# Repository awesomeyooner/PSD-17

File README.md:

# PSD-17

The PSD-21 is an FOC controller designed for stepper motors, specifically for NEMA 17 stepper motors.

Click here for the [manual](./docs/Manual.md)
## Folder Tree

```bash
.
├── esp_test_firmware # Test firmware on ESP32
│   └── firmware # PlatformIO Project
├── firmware # Main firmware (SAMD21)
├── i2c_test # I2C Master Communication Test
│   └── project  # CMake Project
├── pcb # KiCad Project
├── samd21_test_firmware # Test firmware on SAMD21
│   └── firmware # PlatformIO Project
└── README.md
```

## Hardware Details

- [NEMA 17 Motor](https://www.omc-stepperonline.com/nema-17-stepper-motor)
    - [STEPPERONLINE 23mm](https://www.amazon.com/dp/B0B93PNYCP?ref=ppx_yo2ov_dt_b_fed_asin_title&th=1)
    - [STEPPERONLINE 38mm](https://www.amazon.com/dp/B0B38GX54H?ref=ppx_yo2ov_dt_b_fed_asin_title&th=1)
- [AS5047P Magnetic Encoder](https://www.digikey.com/en/products/detail/ams-osram-usa-inc/AS5047P-ADAPTERBOARD/5452344?s=N4IgTCBcDaIIYGcCsAGALAdgA4gLoF8g)
    - [Diametric Magnet](https://www.digikey.com/en/products/detail/radial-magnets-inc/9049/6030786) (6mm x 2.5mm )
- [DRV8874 DC Motor Driver](https://www.pololu.com/product/4035) (2x)
- [SAMD21 Seeed Studio Xiao](https://www.amazon.com/Seeeduino-Smallest-Microcontroller-Interfaces-Compatible/dp/B08745JBRP?th=1)

### Passive Components 

- [5V Voltage Regulator](https://www.pololu.com/product/5433?gQT=1)

## Datasheets

### AS5047P
- [Board](https://www.mouser.com/datasheet/2/588/AS5047P-TS_EK_AB_Operation-Manual_Rev.1.0-775823.pdf)
- [Chip](https://look.ams-osram.com/m/d05ee39221f9857/original/AS5047P-DS000324.pdf)

### DRV8874
- [Board](https://www.pololu.com/product/4035)
- [Chip](https://www.ti.com/lit/ds/symlink/drv8874.pdf)

### SAMD21
- [Seeed Studio Xiao](https://wiki.seeedstudio.com/Seeeduino-XIAO/)
- [SAMD21 Chip](https://ww1.microchip.com/downloads/en/DeviceDoc/SAM_D21_DA1_Family_DataSheet_DS40001882F.pdf)

### NEMA 17
- [23mm](https://www.omc-stepperonline.com/e-series-nema-17-bipolar-1-8deg-17ncm-24-07oz-in-1a-42x42x23mm-4-wires-17he08-1004s)
- [38mm](https://www.omc-stepperonline.com/e-series-nema-17-bipolar-42ncm-59-49oz-in-1-5a-42x42x38mm-4-wires-w-1m-cable-connector-17he15-1504s)

## Contact
Feel free to reach out!
- awesomeyooner@gmail.com

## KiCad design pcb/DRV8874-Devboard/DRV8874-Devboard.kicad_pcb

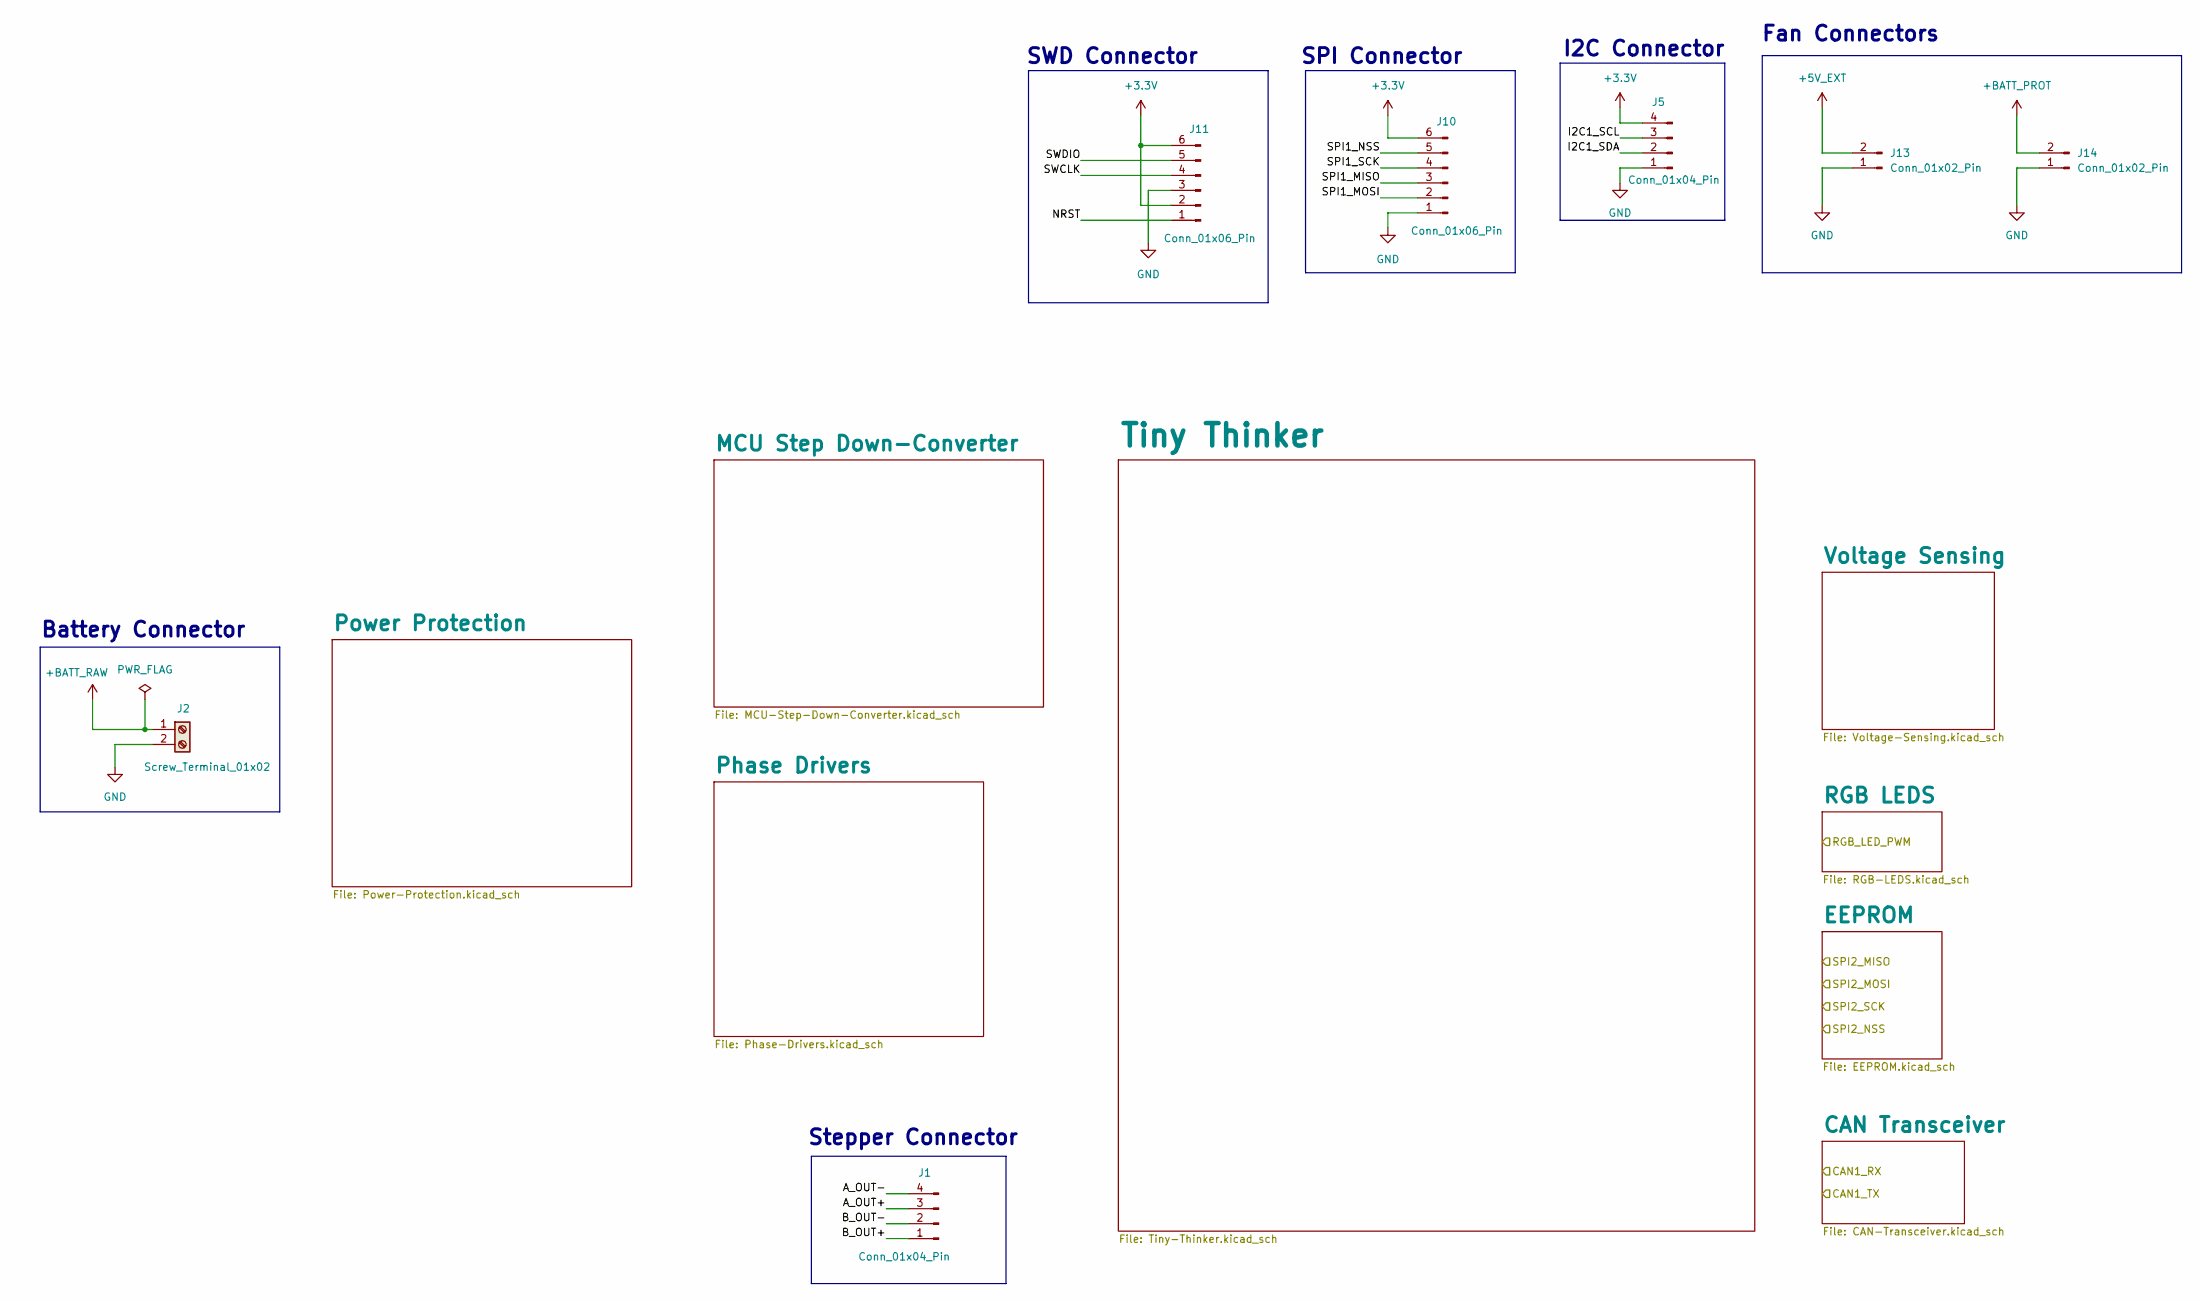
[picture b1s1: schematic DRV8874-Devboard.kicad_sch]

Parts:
J1, J5: Conn_01x04_Pin; PinHeader_1x04_P2.54mm_Vertical
J2: Screw_Terminal_01x02; CONN-TH_2P-P5.08_DB128L-5.08-2P-BK-S; JLCPCB Part # C430601
J10, J11: Conn_01x06_Pin; PinHeader_1x06_P2.54mm_Vertical
J13, J14: Conn_01x02_Pin; PinHeader_1x02_P2.54mm_Vertical

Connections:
+3.3V: J5.4, J10.6, J11.2, J11.6; also elsewhere on the board
+5V_EXT: J13.2; also elsewhere on the board
+BATT_PROT: J14.2; also elsewhere on the board
+BATT_RAW: J2.1; also elsewhere on the board
/A_OUT+: J1.3
/A_OUT-: J1.4
/B_OUT+: J1.1
/B_OUT-: J1.2
/I2C1_SCL: J5.3
/I2C1_SDA: J5.2
/NRST: J11.1
/SPI1_MISO: J10.3
/SPI1_MOSI: J10.2
/SPI1_NSS: J10.5
/SPI1_SCK: J10.4
/SWCLK: J11.4
/SWDIO: J11.5
GND: J2.2, J5.1, J10.1, J11.3, J13.1, J14.1; also elsewhere on the board

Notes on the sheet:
SWD Connector
Fan Connectors
Battery Connector
SPI Connector
Stepper Connector
I2C Connector

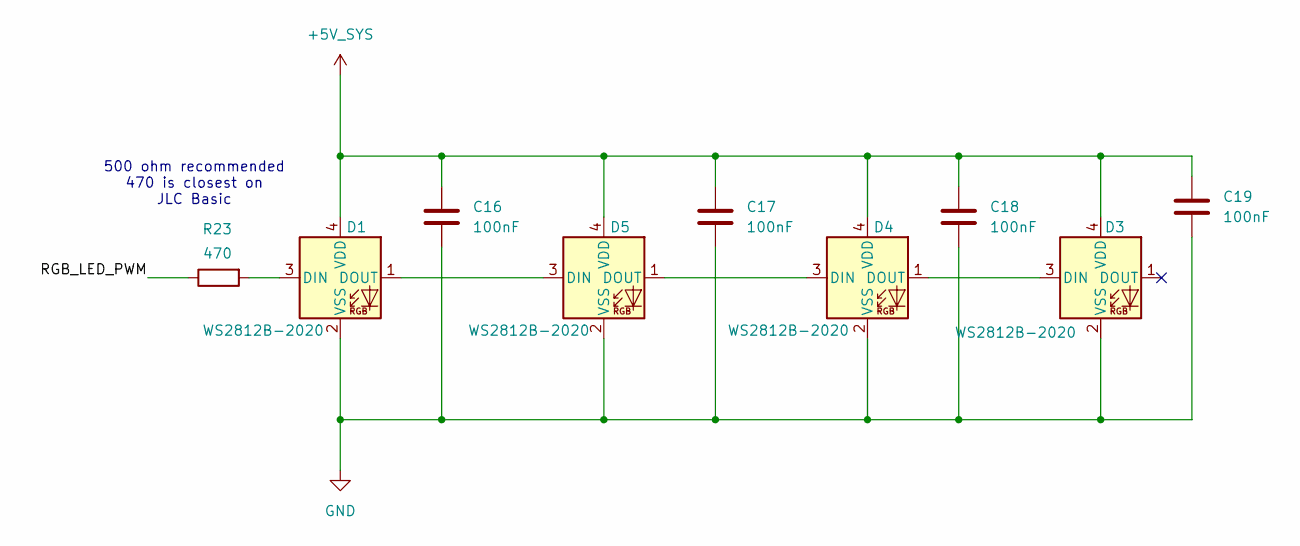
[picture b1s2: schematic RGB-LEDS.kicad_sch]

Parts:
C16, C17, C18, C19: 100nF; C_0402_1005Metric; JLCPCB Part # C307331
D1, D3, D4, D5: WS2812B-2020; LED_WS2812B-2020_PLCC4_2.0x2.0mm; JLCPCB Part # C3646929
R23: 470; R_0402_1005Metric; JLCPCB Part # C25117

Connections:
+5V_SYS: C16.1, C17.1, C18.1, C19.1, D1.4 (VDD), D3.4 (VDD), D4.4 (VDD), D5.4 (VDD); also elsewhere on the board
/RGB LEDS/RGB_LED_PWM: R23.1
GND: C16.2, C17.2, C18.2, C19.2, D1.2 (VSS), D3.2 (VSS), D4.2 (VSS), D5.2 (VSS); also elsewhere on the board
unnamed: D1.3 (DIN), R23.2
unnamed: D1.1 (DOUT), D5.3 (DIN)
unnamed: D3.3 (DIN), D4.1 (DOUT)
unnamed: D4.3 (DIN), D5.1 (DOUT)

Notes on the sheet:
500 ohm recommended 470 is closest on JLC Basic

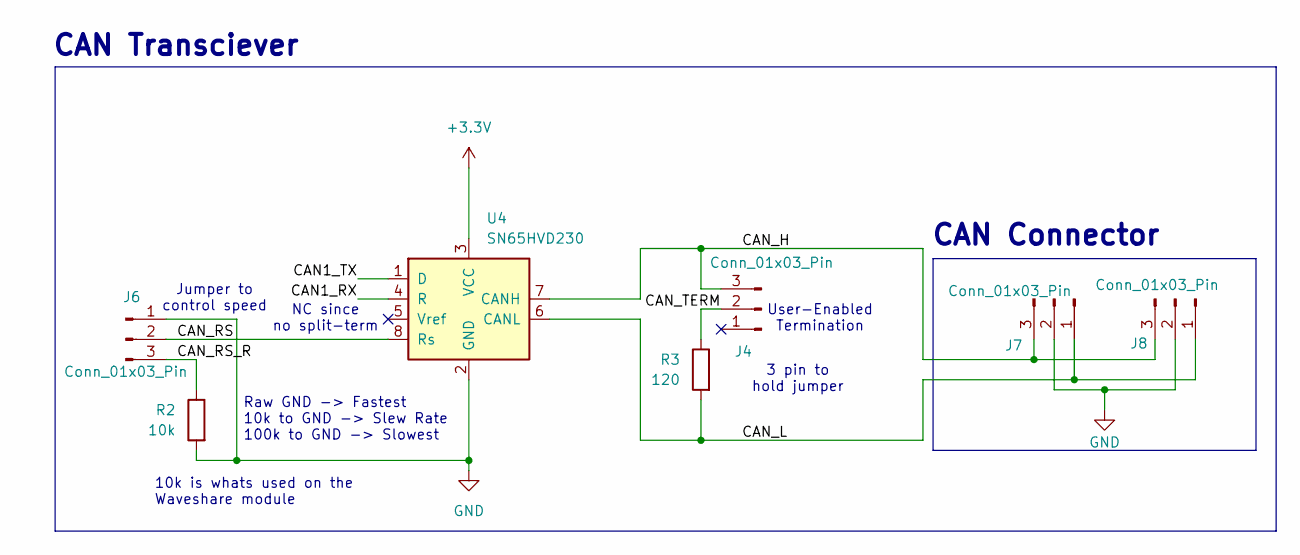
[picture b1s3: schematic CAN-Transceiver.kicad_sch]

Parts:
J4, J6, J7, J8: Conn_01x03_Pin; PinHeader_1x03_P2.54mm_Vertical
R2: 10k; R_0402_1005Metric; JLCPCB Part # C25744
R3: 120; R_0402_1005Metric; JLCPCB Part # C25079
U4: SN65HVD230; SOIC-8_3.9x4.9mm_P1.27mm; JLCPCB Part # C12084

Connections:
+3.3V: U4.3 (VCC); also elsewhere on the board
/CAN Transceiver/CAN1_RX: U4.4 (R)
/CAN Transceiver/CAN1_TX: U4.1 (D)
/CAN Transceiver/CAN_H: J4.3, J7.3, J8.3, U4.7 (CANH)
/CAN Transceiver/CAN_L: J7.1, J8.1, R3.2, U4.6 (CANL)
/CAN Transceiver/CAN_RS: J6.2, U4.8 (Rs)
/CAN Transceiver/CAN_RS_R: J6.3, R2.1
/CAN Transceiver/CAN_TERM: J4.2, R3.1
GND: J6.1, J7.2, J8.2, R2.2, U4.2 (GND); also elsewhere on the board

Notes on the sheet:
Jumper to control speed
10k is whats used on the Waveshare module
CAN Connector
CAN Transciever
Raw GND -> Fastest 10k to GND -> Slew Rate 100k to GND -> Slowest
3 pin to hold jumper
User-Enabled Termination
NC since no split-term

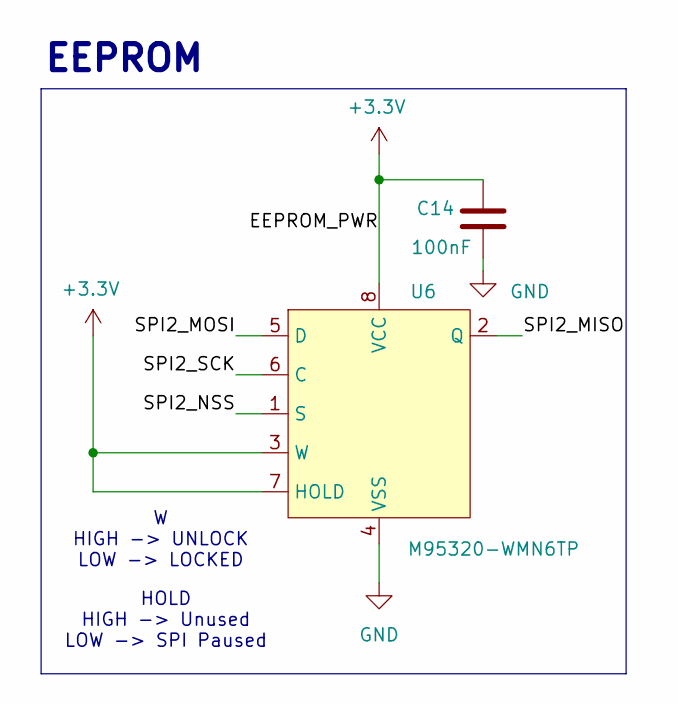
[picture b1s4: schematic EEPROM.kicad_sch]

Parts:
C14: 100nF; C_0402_1005Metric; JLCPCB Part # C307331
U6: M95320-WMN6TP; SO-8_3.9x4.9mm_P1.27mm; JLCPCB Part # C283459

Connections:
+3.3V: C14.1, U6.3 (W), U6.7 (HOLD), U6.8 (VCC); also elsewhere on the board
/EEPROM/SPI2_MISO: U6.2 (Q)
/EEPROM/SPI2_MOSI: U6.5 (D)
/EEPROM/SPI2_NSS: U6.1 (S)
/EEPROM/SPI2_SCK: U6.6 (C)
GND: C14.2, U6.4 (VSS); also elsewhere on the board

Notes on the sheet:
HOLD HIGH -> Unused LOW -> SPI Paused
EEPROM
W HIGH -> UNLOCK LOW -> LOCKED

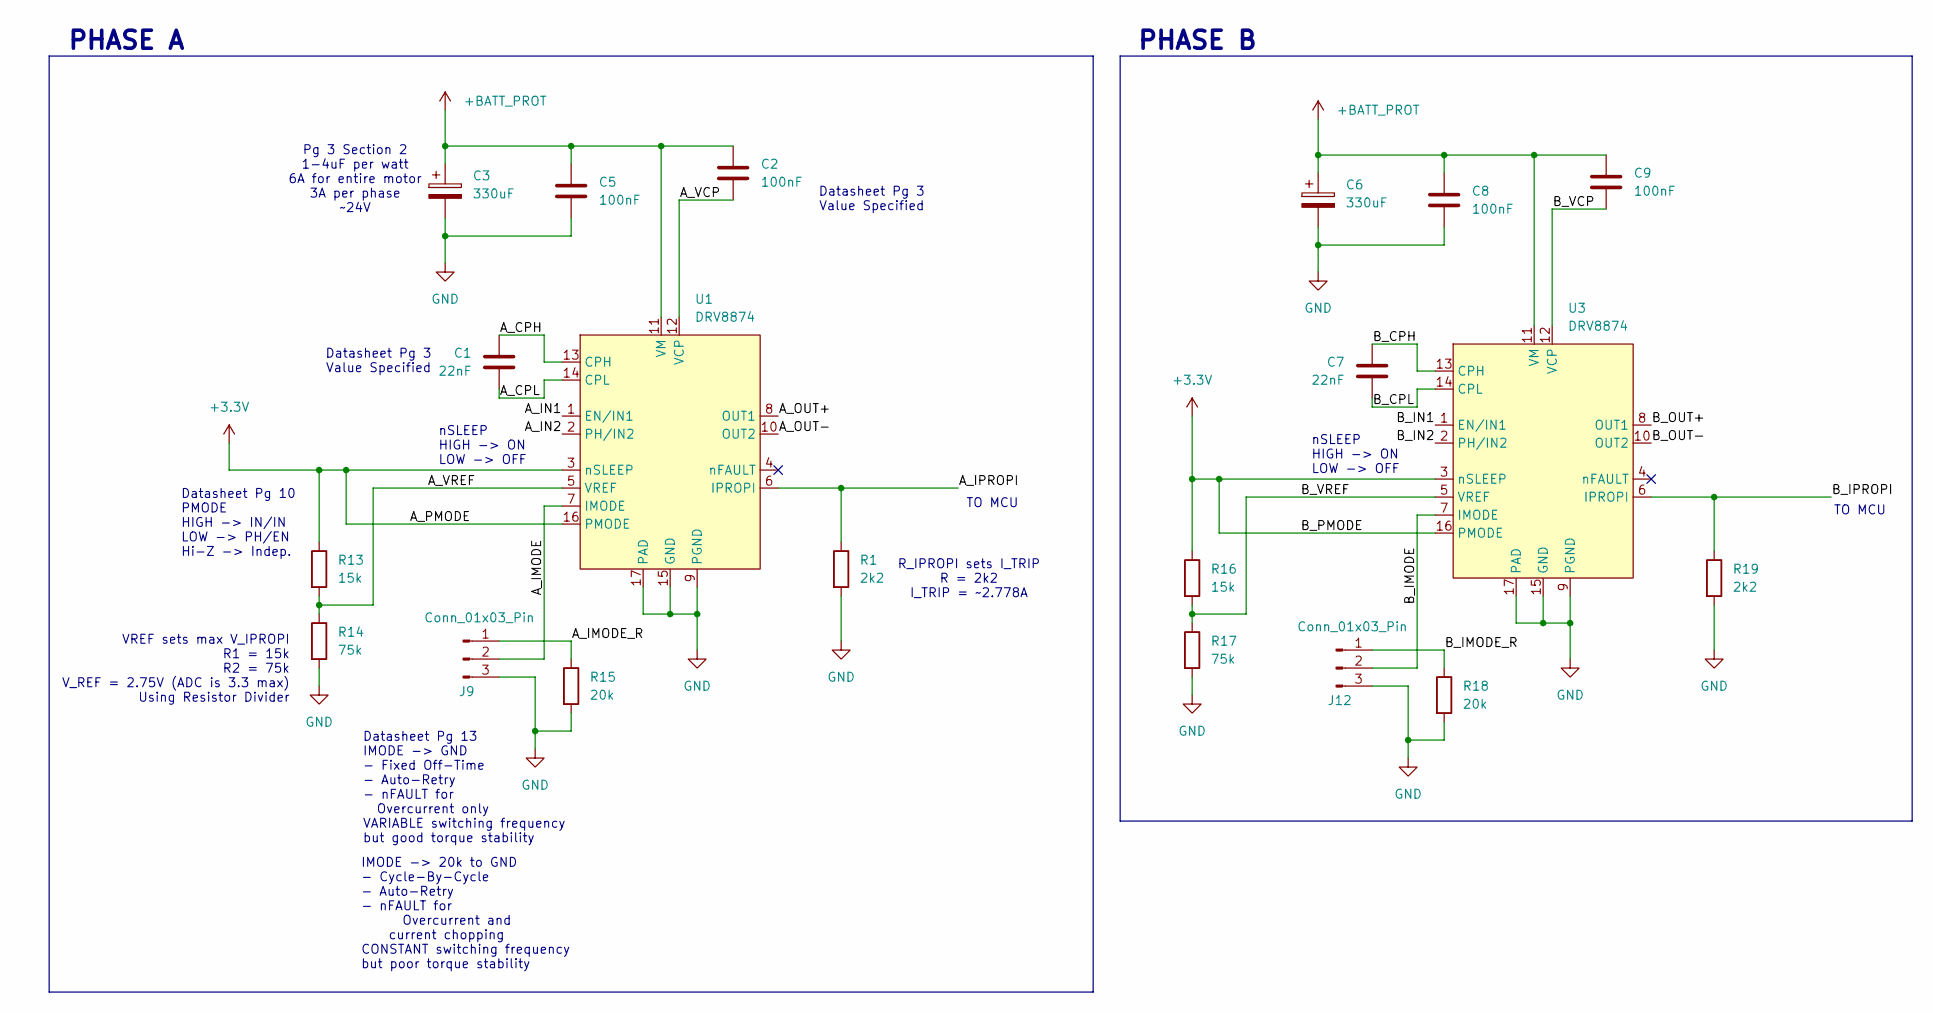
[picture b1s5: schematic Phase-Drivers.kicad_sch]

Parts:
C1, C7: 22nF; C_0402_1005Metric; JLCPCB Part # C1532
C2, C5, C8, C9: 100nF; C_0402_1005Metric; JLCPCB Part # C307331
C3, C6: 330uF; CP_Elec_10x10.5; JLCPCB Part # C46550419
J9, J12: Conn_01x03_Pin; PinHeader_1x03_P2.54mm_Vertical
R1, R19: 2k2; R_0402_1005Metric; JLCPCB Part # C25879
R13, R16: 15k; R_0603_1608Metric; JLCPCB Part # C22809
R14, R17: 75k; R_0603_1608Metric; JLCPCB Part # C23242
R15, R18: 20k; R_0603_1608Metric; JLCPCB Part # C4184
U1, U3: DRV8874; HTSSOP-16-1EP_4.4x5mm_P0.65mm_EP3.4x5mm_Mask2.46x2.31mm; JLCPCB Part # C1855818

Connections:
+3.3V: R13.1, R16.1, U1.3 (nSLEEP), U1.16 (PMODE), U3.3 (nSLEEP), U3.16 (PMODE); also elsewhere on the board
+BATT_PROT: C2.1, C3.1, C5.1, C6.1, C8.1, C9.1, U1.11 (VM), U3.11 (VM); also elsewhere on the board
/Phase Drivers/A_CPH: C1.1, U1.13 (CPH)
/Phase Drivers/A_CPL: C1.2, U1.14 (CPL)
/Phase Drivers/A_IMODE: J9.2, U1.7 (IMODE)
/Phase Drivers/A_IMODE_R: J9.1, R15.1
/Phase Drivers/A_IN1: U1.1 (EN/IN1)
/Phase Drivers/A_IN2: U1.2 (PH/IN2)
/Phase Drivers/A_IPROPI: R1.1, U1.6 (IPROPI)
/Phase Drivers/A_OUT+: U1.8 (OUT1)
/Phase Drivers/A_OUT-: U1.10 (OUT2)
/Phase Drivers/A_VCP: C2.2, U1.12 (VCP)
/Phase Drivers/A_VREF: R13.2, R14.1, U1.5 (VREF)
/Phase Drivers/B_CPH: C7.1, U3.13 (CPH)
/Phase Drivers/B_CPL: C7.2, U3.14 (CPL)
/Phase Drivers/B_IMODE: J12.2, U3.7 (IMODE)
/Phase Drivers/B_IMODE_R: J12.1, R18.1
/Phase Drivers/B_IN1: U3.1 (EN/IN1)
/Phase Drivers/B_IN2: U3.2 (PH/IN2)
/Phase Drivers/B_IPROPI: R19.1, U3.6 (IPROPI)
/Phase Drivers/B_OUT+: U3.8 (OUT1)
/Phase Drivers/B_OUT-: U3.10 (OUT2)
/Phase Drivers/B_VCP: C9.2, U3.12 (VCP)
/Phase Drivers/B_VREF: R16.2, R17.1, U3.5 (VREF)
GND: C3.2, C5.2, C6.2, C8.2, J9.3, J12.3, R1.2, R14.2, R15.2, R17.2, R18.2, R19.2, U1.9 (PGND), U1.15 (GND), U1.17 (PAD), U3.9 (PGND), U3.15 (GND), U3.17 (PAD); also elsewhere on the board

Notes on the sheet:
Datasheet Pg 3 Value Specified
PHASE B
Datasheet Pg 13 IMODE -> GND - Fixed Off-Time - Auto-Retry - nFAULT for Overcurrent only VARIABLE switching frequency but good torque stability
PHASE A
nSLEEP HIGH -> ON LOW -> OFF
VREF sets max V_IPROPI R1 = 15k R2 = 75k V_REF = 2.75V (ADC is 3.3 max) Using Resistor Divider
TO MCU
IMODE -> 20k to GND - Cycle-By-Cycle - Auto-Retry - nFAULT for Overcurrent and current chopping CONSTANT switching frequency but poor torque stability
Pg 3 Section 2 1-4uF per watt 6A for entire motor 3A per phase ~24V
R_IPROPI sets I_TRIP R = 2k2 I_TRIP = ~2.778A
Datasheet Pg 10 PMODE HIGH -> IN/IN LOW -> PH/EN Hi-Z -> Indep.

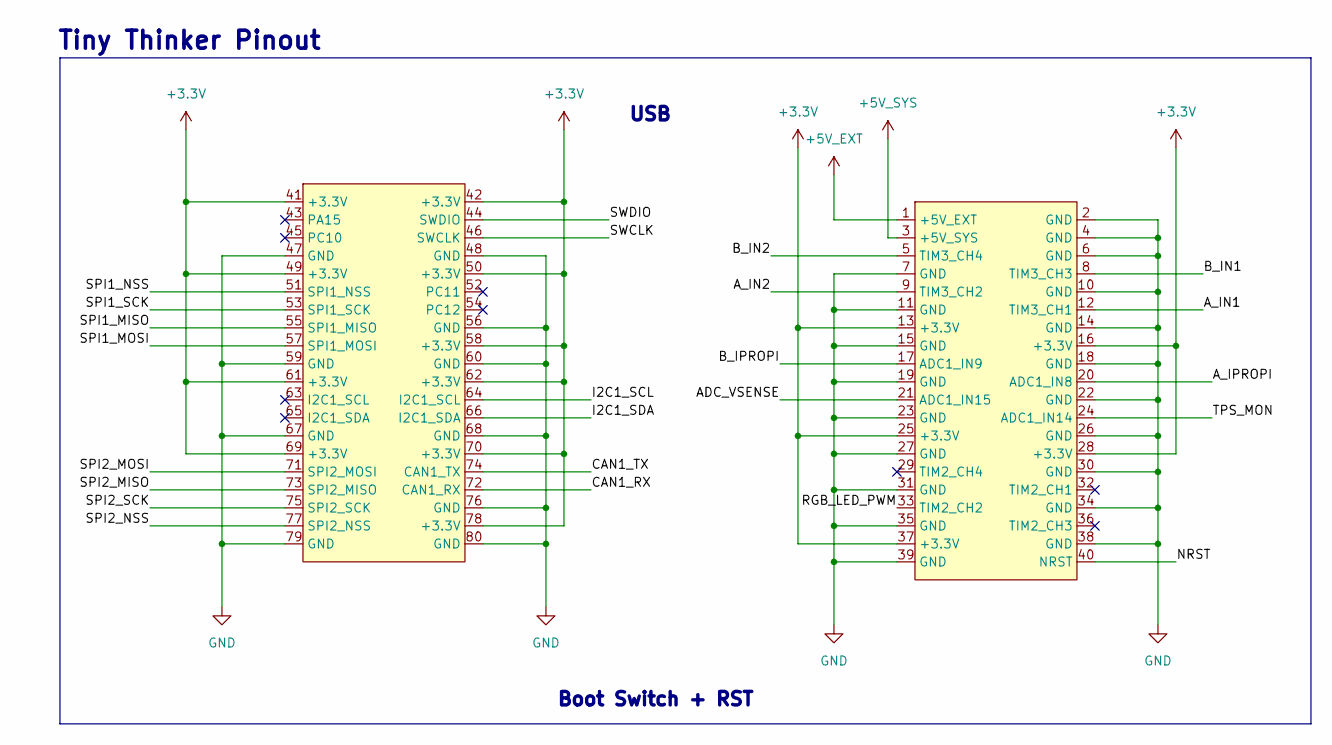
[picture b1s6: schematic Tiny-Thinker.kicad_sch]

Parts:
U7: TinyThinker_J1; TinyThinker_HAT

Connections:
+3.3V: U7.13 (+3.3V), U7.16 (+3.3V), U7.25 (+3.3V), U7.28 (+3.3V), U7.37 (+3.3V), U7.41 (+3.3V), U7.42 (+3.3V), U7.49 (+3.3V), U7.50 (+3.3V), U7.58 (+3.3V), U7.61 (+3.3V), U7.62 (+3.3V), U7.69 (+3.3V), U7.70 (+3.3V), U7.78 (+3.3V); also elsewhere on the board
+5V_EXT: U7.1 (+5V_EXT); also elsewhere on the board
+5V_SYS: U7.3 (+5V_SYS); also elsewhere on the board
/Tiny Thinker/ADC_VSENSE: U7.21 (ADC1_IN15)
/Tiny Thinker/A_IN1: U7.12 (TIM3_CH1)
/Tiny Thinker/A_IN2: U7.9 (TIM3_CH2)
/Tiny Thinker/A_IPROPI: U7.20 (ADC1_IN8)
/Tiny Thinker/B_IN1: U7.8 (TIM3_CH3)
/Tiny Thinker/B_IN2: U7.5 (TIM3_CH4)
/Tiny Thinker/B_IPROPI: U7.17 (ADC1_IN9)
/Tiny Thinker/CAN1_RX: U7.72 (CAN1_RX)
/Tiny Thinker/CAN1_TX: U7.74 (CAN1_TX)
/Tiny Thinker/I2C1_SCL: U7.64 (I2C1_SCL)
/Tiny Thinker/I2C1_SDA: U7.66 (I2C1_SDA)
/Tiny Thinker/NRST: U7.40 (NRST)
/Tiny Thinker/RGB_LED_PWM: U7.33 (TIM2_CH2)
/Tiny Thinker/SPI1_MISO: U7.55 (SPI1_MISO)
/Tiny Thinker/SPI1_MOSI: U7.57 (SPI1_MOSI)
/Tiny Thinker/SPI1_NSS: U7.51 (SPI1_NSS)
/Tiny Thinker/SPI1_SCK: U7.53 (SPI1_SCK)
/Tiny Thinker/SPI2_MISO: U7.73 (SPI2_MISO)
/Tiny Thinker/SPI2_MOSI: U7.71 (SPI2_MOSI)
/Tiny Thinker/SPI2_NSS: U7.77 (SPI2_NSS)
/Tiny Thinker/SPI2_SCK: U7.75 (SPI2_SCK)
/Tiny Thinker/SWCLK: U7.46 (SWCLK)
/Tiny Thinker/SWDIO: U7.44 (SWDIO)
/Tiny Thinker/TPS_MON: U7.24 (ADC1_IN14)
GND: U7.2 (GND), U7.4 (GND), U7.6 (GND), U7.7 (GND), U7.10 (GND), U7.11 (GND), U7.14 (GND), U7.15 (GND), U7.18 (GND), U7.19 (GND), U7.22 (GND), U7.23 (GND), U7.26 (GND), U7.27 (GND), U7.30 (GND), U7.31 (GND), U7.34 (GND), U7.35 (GND), U7.38 (GND), U7.39 (GND), U7.47 (GND), U7.48 (GND), U7.56 (GND), U7.59 (GND), U7.60 (GND), U7.67 (GND), U7.68 (GND), U7.76 (GND), U7.79 (GND), U7.80 (GND); also elsewhere on the board

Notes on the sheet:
Tiny Thinker Pinout
Boot Switch + RST
USB

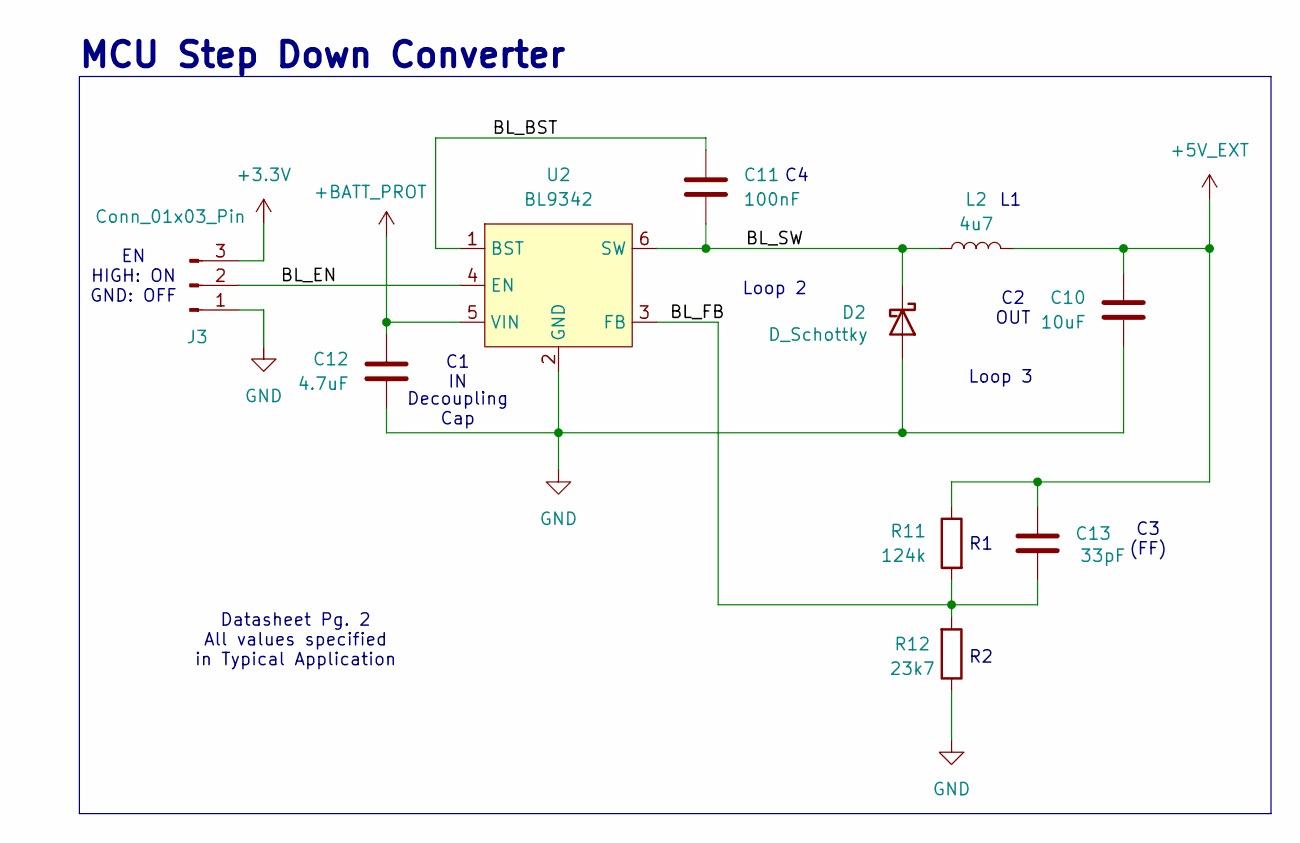
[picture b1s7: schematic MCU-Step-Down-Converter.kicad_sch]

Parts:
C10: 10uF; C_0603_1608Metric; JLCPCB Part # C96446
C11: 100nF; C_0402_1005Metric; JLCPCB Part # C307331
C12: 4.7uF; C_1206_3216Metric; JLCPCB Part # C29823
C13: 33pF; C_0603_1608Metric; JLCPCB Part # C1663
D2: D_Schottky; D_SMA; JLCPCB Part # C2480
J3: Conn_01x03_Pin; PinHeader_1x03_P2.54mm_Vertical
L2: 4u7; L_1008_2520Metric; JLCPCB Part # C5832360
R11: 124k; R_0603_1608Metric; JLCPCB Part # C22788
R12: 23k7; R_0603_1608Metric; JLCPCB Part # C2933175
U2: BL9342; SOT-23-6; JLCPCB Part # C93176

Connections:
+3.3V: J3.3; also elsewhere on the board
+5V_EXT: C10.1, C13.2, L2.2, R11.1; also elsewhere on the board
+BATT_PROT: C12.1, U2.5 (VIN); also elsewhere on the board
/MCU Step Down-Converter/BL_BST: C11.1, U2.1 (BST)
/MCU Step Down-Converter/BL_EN: J3.2, U2.4 (EN)
/MCU Step Down-Converter/BL_FB: C13.1, R11.2, R12.2, U2.3 (FB)
/MCU Step Down-Converter/BL_SW: C11.2, D2.1 (K), L2.1, U2.6 (SW)
GND: C10.2, C12.2, D2.2 (A), J3.1, R12.1, U2.2 (GND); also elsewhere on the board

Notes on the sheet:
MCU Step Down Converter
C2 OUT
Datasheet Pg. 2 All values specified in Typical Application
C3 (FF)
Loop 3
Decoupling Cap
Loop 2
EN HIGH: ON GND: OFF
C1 IN

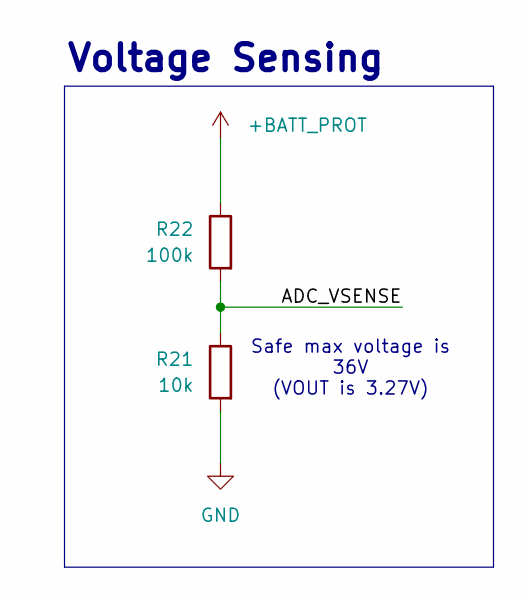
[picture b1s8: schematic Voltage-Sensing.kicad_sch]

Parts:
R21: 10k; R_0402_1005Metric; JLCPCB Part # C25744
R22: 100k; R_0603_1608Metric; JLCPCB Part # C25803

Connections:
+BATT_PROT: R22.1; also elsewhere on the board
/Voltage Sensing/ADC_VSENSE: R21.1, R22.2
GND: R21.2; also elsewhere on the board

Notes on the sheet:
Voltage Sensing
Safe max voltage is 36V (VOUT is 3.27V)

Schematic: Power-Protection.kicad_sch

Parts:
C4: 33nF; C_0603_1608Metric; JLCPCB Part # C21117
C15: 100nF; C_0402_1005Metric; JLCPCB Part # C307331
R5: 3k; R_0603_1608Metric; JLCPCB Part # C4211
R6: 10k; R_0402_1005Metric; JLCPCB Part # C25744
R7: 18k; R_0603_1608Metric; JLCPCB Part # C25810
R8: 510k; R_0603_1608Metric; JLCPCB Part # C23192
R9: 100k; R_0603_1608Metric; JLCPCB Part # C25803
R10: 20k; R_0603_1608Metric; JLCPCB Part # C4184
U5: TPS16630PWPR; HTSSOP20_PWP_TEX; JLCPCB Part # C1849461

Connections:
+3.3V: R6.1, U5.13 (*SHDN); also elsewhere on the board
+BATT_PROT: U5.18 (OUT), U5.19 (OUT), U5.20 (OUT); also elsewhere on the board
+BATT_RAW: C15.2, R8.1, U5.1 (IN), U5.2 (IN), U5.3 (IN), U5.6 (P_IN); also elsewhere on the board
/Power Protection/TPS_DVDT: C4.1, U5.10 (DVDT)
/Power Protection/TPS_FLT: R6.2, U5.15 (*FLT)
/Power Protection/TPS_ILIM: R5.1, U5.11 (ILIM)
/Power Protection/TPS_MON: R7.1, U5.14 (IMON)
/Power Protection/TPS_OVP: R9.2, R10.1, U5.8 (OVP)
/Power Protection/TPS_UVLO: R8.2, R9.1, U5.7 (UVLO)
GND: C4.2, C15.1, R5.2, R7.2, R10.2, U5.9 (GND), U5.12 (MODE), U5.21 (GND); also elsewhere on the board

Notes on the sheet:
Power Protection
IMON 18k ~3V @ 6A
MODE -> GND Auto-Retry
to STM32
33nF => 1A ~15ms
UVLO ~6V OVP ~38V
Datasheet Pg 28 9.2.2.2 R's Calc
Max V: 36V Min V: 6V (for DRV8874)
FLT HIGH: Norm LOW: Fault
SHDN HIGH: ON GND: OFF
100nF Decoupling Cap
I_OL = 6A

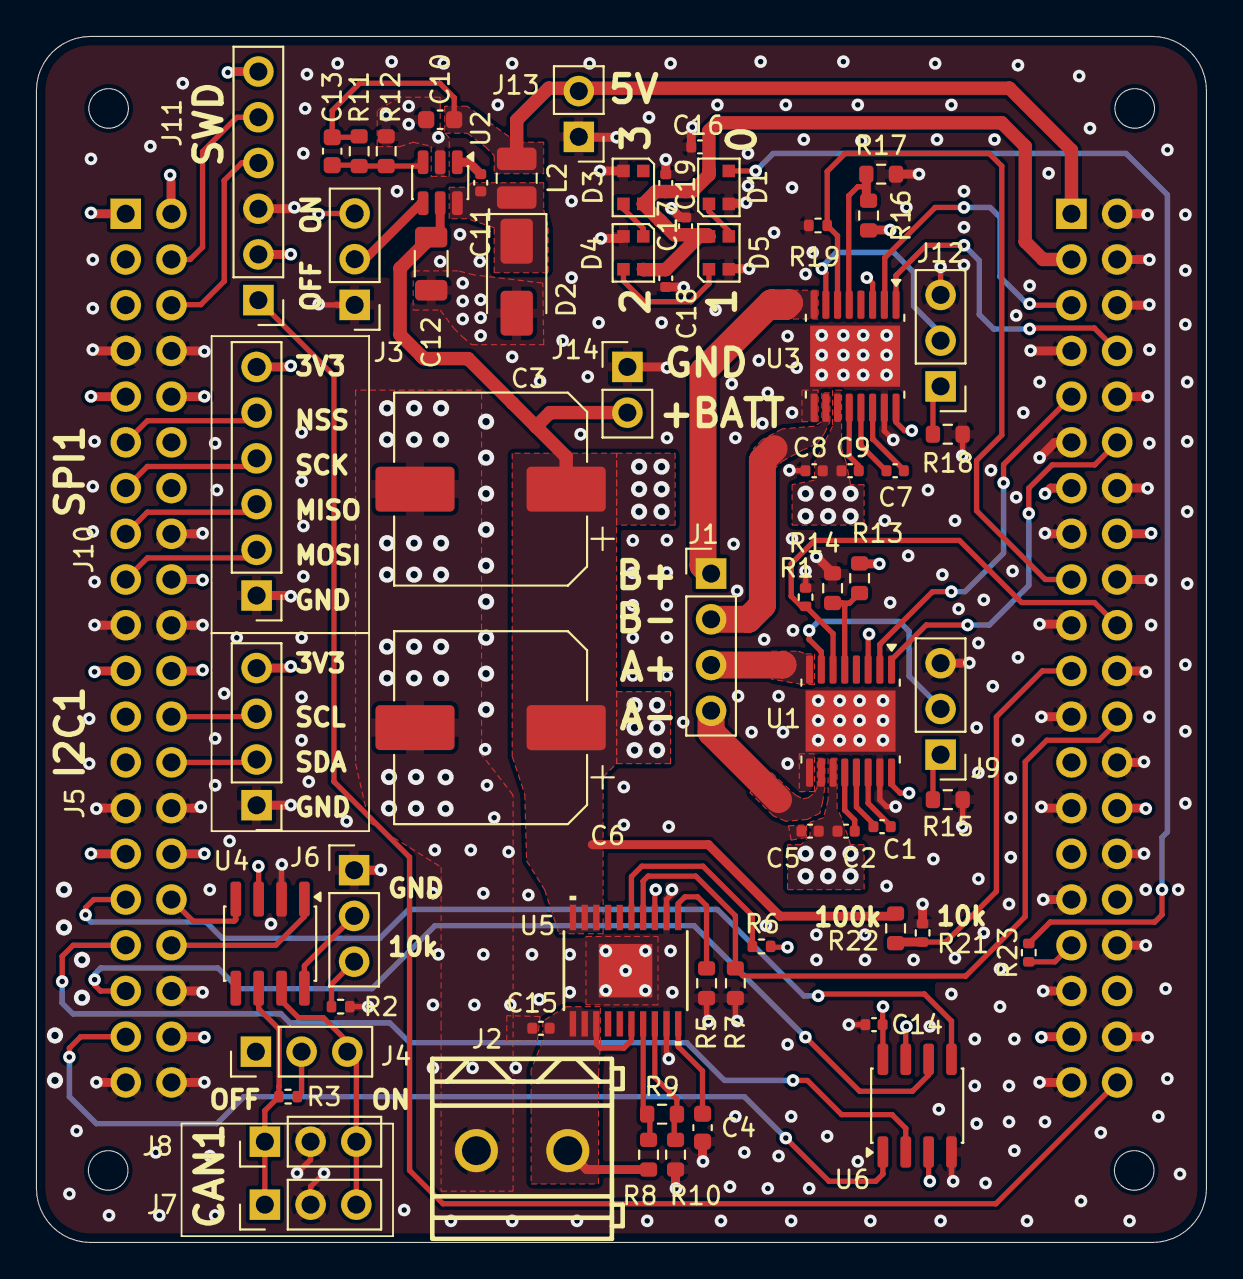
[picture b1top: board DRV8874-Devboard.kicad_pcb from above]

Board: 4 copper layers, 65.0 x 67.0 mm, 67 parts (1 on the bottom side), 40 nets.

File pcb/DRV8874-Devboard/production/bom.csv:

Designator,Footprint,Quantity,Value,LCSC Part #
"C1, C7",0402,2,22nF, C1532
C10,0603,1,10uF,C96446
"C11, C14, C15, C16, C17, C18, C19, C2, C5, C8, C9",0402,11,100nF, C307331
C12,1206,1,4.7uF,C29823
C13,0603,1,33pF, C1663
"C3, C6",CP_Elec_10x10.5,2,330uF,C46550419
C4,0603,1,33nF, C21117
"D1, D3, D4, D5",LED_WS2812B-2020_PLCC4_2.0x2.0mm,4,WS2812B-2020,C3646929
D2,D_SMA,1,D_Schottky,C2480
"J1, J5",PinHeader_1x04_P2.54mm_Vertical,2,Conn_01x04_Pin,
"J10, J11",PinHeader_1x06_P2.54mm_Vertical,2,Conn_01x06_Pin,
"J12, J3, J4, J6, J7, J8, J9",PinHeader_1x03_P2.54mm_Vertical,7,Conn_01x03_Pin,
"J13, J14",PinHeader_1x02_P2.54mm_Vertical,2,Conn_01x02_Pin,
J2,CONN-TH_2P-P5.08_DB128L-5.08-2P-BK-S,1,Screw_Terminal_01x02,C430601
L2,1008,1,4u7,C5832360
"R1, R19",0402,2,2k2, C25879
"R10, R15, R18",0603,3,20k,C4184
R11,0603,1,124k,C22788
R12,0603,1,23k7,C2933175
"R13, R16",0603,2,15k,C22809
"R14, R17",0603,2,75k,C23242
"R2, R21, R6",0402,3,10k,C25744
"R22, R9",0603,2,100k,C25803
R23,0402,1,470,C25117
R3,0402,1,120,C25079
R5,0603,1,3k,C4211
R7,0603,1,18k, C25810
R8,0603,1,510k,C23192
"U1, U3",HTSSOP-16-1EP_4.4x5mm_P0.65mm_EP3.4x5mm_Mask2.46x2.31mm,2,DRV8874,C1855818
U2,SOT-23-6,1,BL9342,C93176
U4,SOIC-8_3.9x4.9mm_P1.27mm,1,SN65HVD230,C12084
U5,HTSSOP20_PWP_TEX,1,TPS16630PWPR,C1849461
U6,SO-8_3.9x4.9mm_P1.27mm,1,M95320-WMN6TP,C283459
U7,TinyThinker_HAT,1,TinyThinker_J1,C1525

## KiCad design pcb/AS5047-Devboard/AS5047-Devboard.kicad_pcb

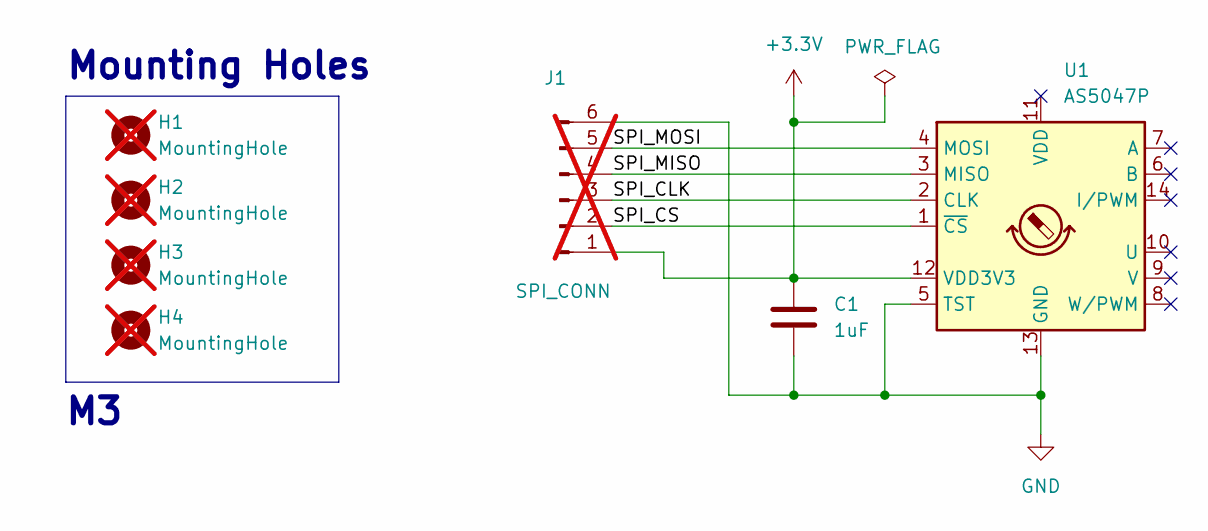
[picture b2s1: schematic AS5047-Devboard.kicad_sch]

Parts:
C1: 1uF; C_0603_1608Metric; JLCPCB Part # C15849
H1, H2, H3, H4: MountingHole; MountingHole_3.2mm_M3; not fitted
J1: SPI_CONN; PinHeader_1x06_P2.54mm_Vertical; not fitted
U1: AS5047P; TSSOP-14_4.4x5mm_P0.65mm; JLCPCB Part # C962063

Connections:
+3.3V: C1.1, J1.1, U1.12 (VDD3V3)
/SPI_CLK: J1.3, U1.2 (CLK)
/SPI_CS: J1.2, U1.1 (~CS)
/SPI_MISO: J1.4, U1.3 (MISO)
/SPI_MOSI: J1.5, U1.4 (MOSI)
GND: C1.2, J1.6, U1.5 (TST), U1.13 (GND)

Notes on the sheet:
Mounting Holes

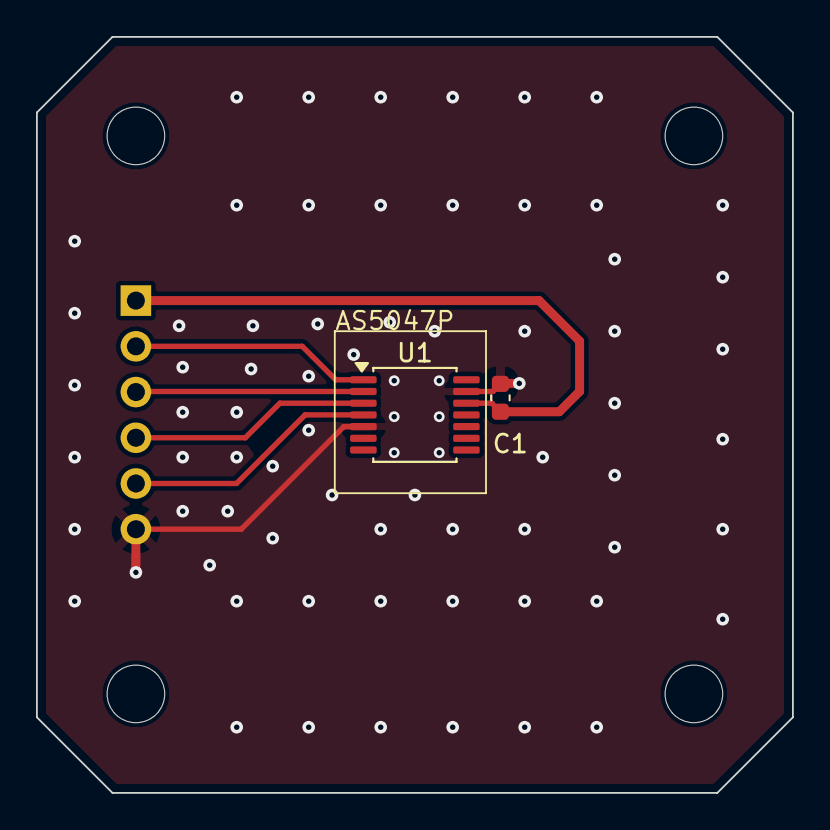
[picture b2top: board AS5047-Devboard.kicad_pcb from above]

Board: 2 copper layers, 42.0 x 42.0 mm, 7 parts (1 on the bottom side), 6 nets.

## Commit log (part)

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2025-07-17 added initial kicad project
2025-07-21 added basic firmware project
2025-07-22 added basic example
2025-07-23 added test firmware for simplefoc
2025-07-24 push for now
2025-07-24 added test firmware for samd21
2025-07-31 added gitignore
2025-07-31 updated gitignore
2025-07-31 removed build
2025-07-31 renamed file tree
2025-08-01 updated readme to have nema17 specs
2025-08-04 updated readme to include more motors
2025-08-04 changed pins to use DRV8874
2025-08-05 added seperate docs section
2025-08-05 added link to the manual from the README
2025-08-05 it works
2025-08-05 changed arrays to vectors
2025-08-05 commented
2025-08-05 added wrapper class for i2c_device
2025-08-05 wrote wrappers for converting float to bytes and vise versa
2025-08-05 added enum class for command / request types
2025-08-05 updated manual
2025-08-05 started name init
2025-08-05 added logger
2025-08-05 moved status and util to /util folder
2025-08-06 added spi sensor
2025-08-06 switched pins
2025-08-08 added simplefocdrivers
2025-08-08 added dedicated AS5047 driver
2025-08-09 added esp32 firmware
2025-08-11 working
2025-08-11 added new library
2025-08-11 made builtinled static
2025-08-11 used static led
2025-08-12 changed project folders and rewrote manual
2025-08-12 switched firmware samd21 -> esp32
2025-08-12 added back as5047p pic
2025-08-12 moved pics
2025-08-12 added i2c test for esp32
2025-08-15 added i2c test
2025-08-20 logs
2025-08-23 added new project
2025-08-23 added i2c test samd21 and esp32
2025-08-23 working test
2025-08-23 added lines to disable i2c pullup resistors on esp32
2025-08-23 added frequency changes to esp32
2025-08-28 added stm32 nucelo tests
2025-08-28 float example
2025-08-28 working foc example for stm32
2025-09-03 changed include
2025-09-04 changed main firmware to be stm32f446re instead of esp32
2025-09-04 first test of i2c protol
2025-09-04 added abstraction for foc motor
2025-09-04 fixed sensor 0 issue
2025-09-04 started writing registers
2025-09-04 testing i2c
2025-09-04 added functions to create easy commands and requests
2025-09-04 added driver for master side
2025-09-04 cleaned up main (removed Commander)
2025-09-05 added rest of registers
2025-09-05 changed schemes
2025-09-05 added data plotting
2025-09-12 only command sending
2025-09-30 updated plotter
2025-09-30 changed current method to FOCCurrent
2025-09-30 added logs
2025-10-06 updated plotter to have plotting and pushing data seperate, also added documentation
2025-10-06 swapped current pins for phase A and B and also added sensor offset + predetermined zero electric angle (skips alignemtn)
2025-10-06 added new status code and added user input methods
2025-10-06 added custom to_string method for precision retension
2025-10-06 updated plotter to have precise time, not sure how this didn't work before
2025-10-06 added seperate threads for input, plotting, and main communication
2025-10-16 updated pins
2025-10-16 changed pins to allow for timer synchronization
2025-10-16 added auto scroll to plotter
2025-10-16 testing otu different currents
2025-10-16 added auto calibration
2025-10-23 added enable on startup
2025-12-03 added adc sampling time
2025-12-03 added initial schematic for protoboard
2025-12-03 added components
2025-12-04 finished schematic for protoboard
2025-12-04 added more schematics
2025-12-04 changed current
2025-12-05 added perfboard
2025-12-05 started perfboard layout
2025-12-16 added new line for DC currnet
2025-12-16 added new run logs
2025-12-16 updated protoboard for shield perfboard
2025-12-16 updated gitignore to ignore all log files
2025-12-26 changed spi variable
2025-12-26 changed CS pin
2025-12-31 updated schematic
2025-12-31 add plib
2026-01-01 update plib
2026-01-06 removed all old plib files and added the git submodule
2026-01-06 Updated plib
2026-01-06 misc changes
2026-01-06 updated plib to use correct i2c path
2026-01-06 made the flag public in implotter
2026-01-06 updated plib and seperated plotter to be at called within main itself and not a lambda
2026-01-06 added more requests
2026-01-16 added new submodules
2026-01-16 removed unused platformio projects
2026-01-16 removed more unused projects
2026-01-16 added testbench for stm32f446
2026-01-16 added custom file for AS5047 sensor
2026-01-16 changed defines to constexprs
2026-01-22 updated testbench
2026-02-13 Added AS5047 Devboard for NEMA17
2026-02-13 updated ground pour
2026-02-13 DNP mounting holes
2026-02-13 unlocked file
2026-02-17 added DRV8874 initial schematic
2026-02-19 unlock
2026-02-22 moved AS5047 Devboard out one directory
2026-02-22 updated AS5047P board to include stitching vias
2026-02-22 unlocked AS5047P files
2026-02-22 updated BOM
2026-02-23 added CAN transciever
2026-02-24 exposed more connectors on DRV8874 devb
2026-02-24 Updated sensor coorindates for AS5047P
2026-03-07 added tiny thinker firmware
2026-03-10 Added new abstractions
2026-03-14 updated spi
2026-03-14 updated spi again
2026-03-14 spi finally works
2026-03-14 bruh I switched the silkscreen
2026-03-17 started working on drv8874
2026-03-17 added USBFS callbacks
2026-03-26 minor changes to DRV8874
2026-04-03 worked on DRV8874
2026-04-04 started working on TPS16630
2026-04-04 finished first iteration of TPS16630 implementation
2026-04-05 unlocked files
2026-04-05 updated DRV8874 to have tinythinker footprint
2026-04-12 changed capacitor symbol to polarized
2026-04-24 added libserial
2026-05-05 started working on serial
2026-05-05 started working on BL9342

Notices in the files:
README.md:
License: MIT
